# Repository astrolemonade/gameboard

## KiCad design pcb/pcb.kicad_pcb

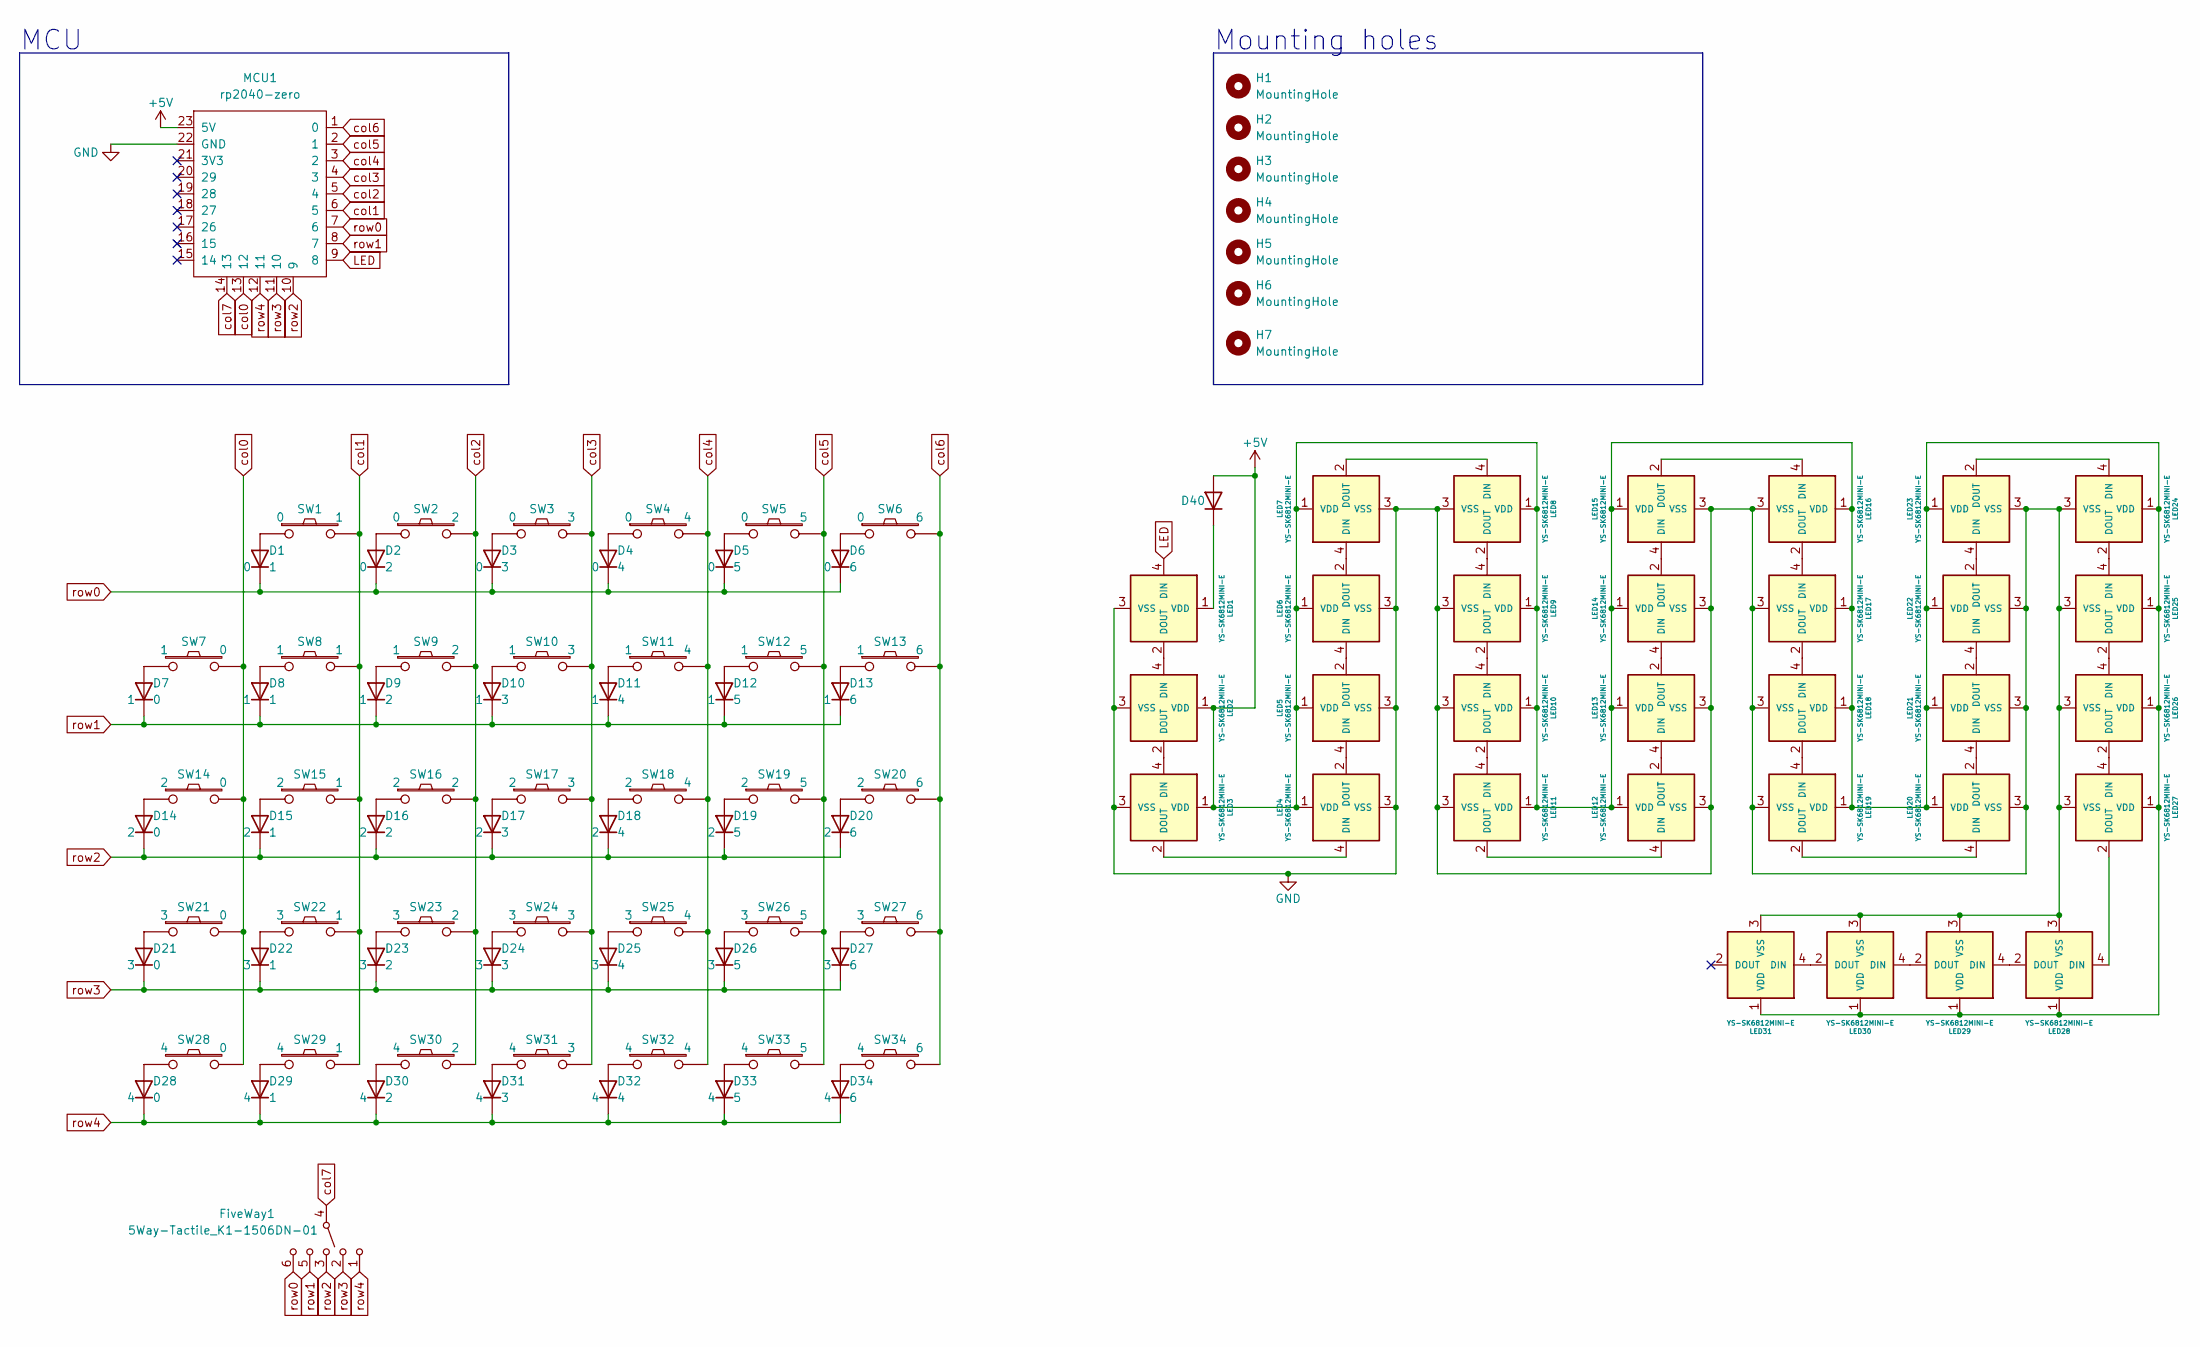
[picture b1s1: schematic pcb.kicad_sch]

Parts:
D1, D2, D3, D4, D5, D6, D7, D8, D9, D10, D11, D12, D13, D14, D15, D16, D17, D18, D19, D20, D21, D22, D23, D24, D25, D26, D27, D28, D29, D30, D31, D32, D33, D34, D40: D; Diode_1N4148-SOD123
FiveWay1: 5Way-Tactile_K1-1506DN-01; Button_5way
H1, H2, H3, H4, H5, H6, H7: MountingHole; Hole_M2-TH
LED1, LED2, LED3, LED4, LED5, LED6, LED7, LED8, LED9, LED10, LED11, LED12, LED13, LED14, LED15, LED16, LED17, LED18, LED19, LED20, LED21, LED22, LED23, LED24, LED25, LED26, LED27, LED28, LED29, LED30, LED31: YS-SK6812MINI-E; LED_SK6812-MINI-E
MCU1: rp2040-zero; MCU_rp2040-zero-tht
SW1, SW2, SW3, SW4, SW5, SW6, SW7, SW8, SW9, SW10, SW11, SW12, SW13, SW14, SW15, SW16, SW17, SW18, SW19, SW20, SW21, SW22, SW23, SW24, SW25, SW26, SW27, SW31, SW32, SW33, SW34: Switch; Switch_MXKS-hotswap-south-ks3d
SW28, SW29, SW30: Switch; Button_Push-6mm

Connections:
+5V: D40.2 (A), LED2.1 (VDD), LED3.1 (VDD), LED4.1 (VDD), LED5.1 (VDD), LED6.1 (VDD), LED7.1 (VDD), LED8.1 (VDD), LED9.1 (VDD), LED10.1 (VDD), LED11.1 (VDD), LED12.1 (VDD), LED13.1 (VDD), LED14.1 (VDD), LED15.1 (VDD), LED16.1 (VDD), LED17.1 (VDD), LED18.1 (VDD), LED19.1 (VDD), LED20.1 (VDD), LED21.1 (VDD), LED22.1 (VDD), LED23.1 (VDD), LED24.1 (VDD), LED25.1 (VDD), LED26.1 (VDD), LED27.1 (VDD), LED28.1 (VDD), LED29.1 (VDD), LED30.1 (VDD), LED31.1 (VDD), MCU1.23 (5V)
GND: LED1.3 (VSS), LED2.3 (VSS), LED3.3 (VSS), LED4.3 (VSS), LED5.3 (VSS), LED6.3 (VSS), LED7.3 (VSS), LED8.3 (VSS), LED9.3 (VSS), LED10.3 (VSS), LED11.3 (VSS), LED12.3 (VSS), LED13.3 (VSS), LED14.3 (VSS), LED15.3 (VSS), LED16.3 (VSS), LED17.3 (VSS), LED18.3 (VSS), LED19.3 (VSS), LED20.3 (VSS), LED21.3 (VSS), LED22.3 (VSS), LED23.3 (VSS), LED24.3 (VSS), LED25.3 (VSS), LED26.3 (VSS), LED27.3 (VSS), LED28.3 (VSS), LED29.3 (VSS), LED30.3 (VSS), LED31.3 (VSS), MCU1.22 (GND)
LED: LED1.4 (DIN), MCU1.9 (8)
unnamed: D1.2 (A), SW1.1
unnamed: D2.2 (A), SW2.1
unnamed: D3.2 (A), SW3.1
unnamed: D4.2 (A), SW4.1
unnamed: D5.2 (A), SW5.1
unnamed: D6.2 (A), SW6.1
unnamed: D7.2 (A), SW7.1
unnamed: D8.2 (A), SW8.1
unnamed: D9.2 (A), SW9.1
unnamed: D10.2 (A), SW10.1
unnamed: D11.2 (A), SW11.1
unnamed: D12.2 (A), SW12.1
unnamed: D13.2 (A), SW13.1
unnamed: D14.2 (A), SW14.1
unnamed: D15.2 (A), SW15.1
unnamed: D16.2 (A), SW16.1
unnamed: D17.2 (A), SW17.1
unnamed: D18.2 (A), SW18.1
unnamed: D19.2 (A), SW19.1
unnamed: D20.2 (A), SW20.1
unnamed: D21.2 (A), SW21.1
unnamed: D22.2 (A), SW22.1
unnamed: D23.2 (A), SW23.1
unnamed: D24.2 (A), SW24.1
unnamed: D25.2 (A), SW25.1
unnamed: D26.2 (A), SW26.1
unnamed: D27.2 (A), SW27.1
unnamed: D28.2 (A), SW28.1
unnamed: D29.2 (A), SW29.1
unnamed: D30.2 (A), SW30.1
unnamed: D31.2 (A), SW31.1
unnamed: D32.2 (A), SW32.1
unnamed: D33.2 (A), SW33.1
unnamed: D34.2 (A), SW34.1
unnamed: D40.1 (K), LED1.1 (VDD)
unnamed: LED1.2 (DOUT), LED2.4 (DIN)
unnamed: LED2.2 (DOUT), LED3.4 (DIN)
unnamed: LED3.2 (DOUT), LED4.4 (DIN)
unnamed: LED4.2 (DOUT), LED5.4 (DIN)
unnamed: LED5.2 (DOUT), LED6.4 (DIN)
unnamed: LED6.2 (DOUT), LED7.4 (DIN)
unnamed: LED7.2 (DOUT), LED8.4 (DIN)
unnamed: LED8.2 (DOUT), LED9.4 (DIN)
unnamed: LED9.2 (DOUT), LED10.4 (DIN)
unnamed: LED10.2 (DOUT), LED11.4 (DIN)
unnamed: LED11.2 (DOUT), LED12.4 (DIN)
unnamed: LED12.2 (DOUT), LED13.4 (DIN)
unnamed: LED13.2 (DOUT), LED14.4 (DIN)
unnamed: LED14.2 (DOUT), LED15.4 (DIN)
unnamed: LED15.2 (DOUT), LED16.4 (DIN)
unnamed: LED16.2 (DOUT), LED17.4 (DIN)
unnamed: LED17.2 (DOUT), LED18.4 (DIN)
unnamed: LED18.2 (DOUT), LED19.4 (DIN)
unnamed: LED19.2 (DOUT), LED20.4 (DIN)
unnamed: LED20.2 (DOUT), LED21.4 (DIN)
unnamed: LED21.2 (DOUT), LED22.4 (DIN)
unnamed: LED22.2 (DOUT), LED23.4 (DIN)
unnamed: LED23.2 (DOUT), LED24.4 (DIN)
unnamed: LED24.2 (DOUT), LED25.4 (DIN)
unnamed: LED25.2 (DOUT), LED26.4 (DIN)
unnamed: LED26.2 (DOUT), LED27.4 (DIN)
unnamed: LED27.2 (DOUT), LED28.4 (DIN)
unnamed: LED28.2 (DOUT), LED29.4 (DIN)
unnamed: LED29.2 (DOUT), LED30.4 (DIN)
unnamed: LED30.2 (DOUT), LED31.4 (DIN)
col0: MCU1.13 (12), SW7.2, SW14.2, SW21.2, SW28.2
col1: MCU1.6 (5), SW1.2, SW8.2, SW15.2, SW22.2, SW29.2
col2: MCU1.5 (4), SW2.2, SW9.2, SW16.2, SW23.2, SW30.2
col3: MCU1.4 (3), SW3.2, SW10.2, SW17.2, SW24.2, SW31.2
col4: MCU1.3 (2), SW4.2, SW11.2, SW18.2, SW25.2, SW32.2
col5: MCU1.2 (1), SW5.2, SW12.2, SW19.2, SW26.2, SW33.2
col6: MCU1.1 (0), SW6.2, SW13.2, SW20.2, SW27.2, SW34.2
col7: FiveWay1.4, MCU1.14 (13)
row0: D1.1 (K), D2.1 (K), D3.1 (K), D4.1 (K), D5.1 (K), D6.1 (K), FiveWay1.6, MCU1.7 (6)
row1: D7.1 (K), D8.1 (K), D9.1 (K), D10.1 (K), D11.1 (K), D12.1 (K), D13.1 (K), FiveWay1.5, MCU1.8 (7)
row2: D14.1 (K), D15.1 (K), D16.1 (K), D17.1 (K), D18.1 (K), D19.1 (K), D20.1 (K), FiveWay1.3, MCU1.10 (9)
row3: D21.1 (K), D22.1 (K), D23.1 (K), D24.1 (K), D25.1 (K), D26.1 (K), D27.1 (K), FiveWay1.2, MCU1.11 (10)
row4: D28.1 (K), D29.1 (K), D30.1 (K), D31.1 (K), D32.1 (K), D33.1 (K), D34.1 (K), FiveWay1.1, MCU1.12 (11)

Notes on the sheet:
Mounting holes
MCU

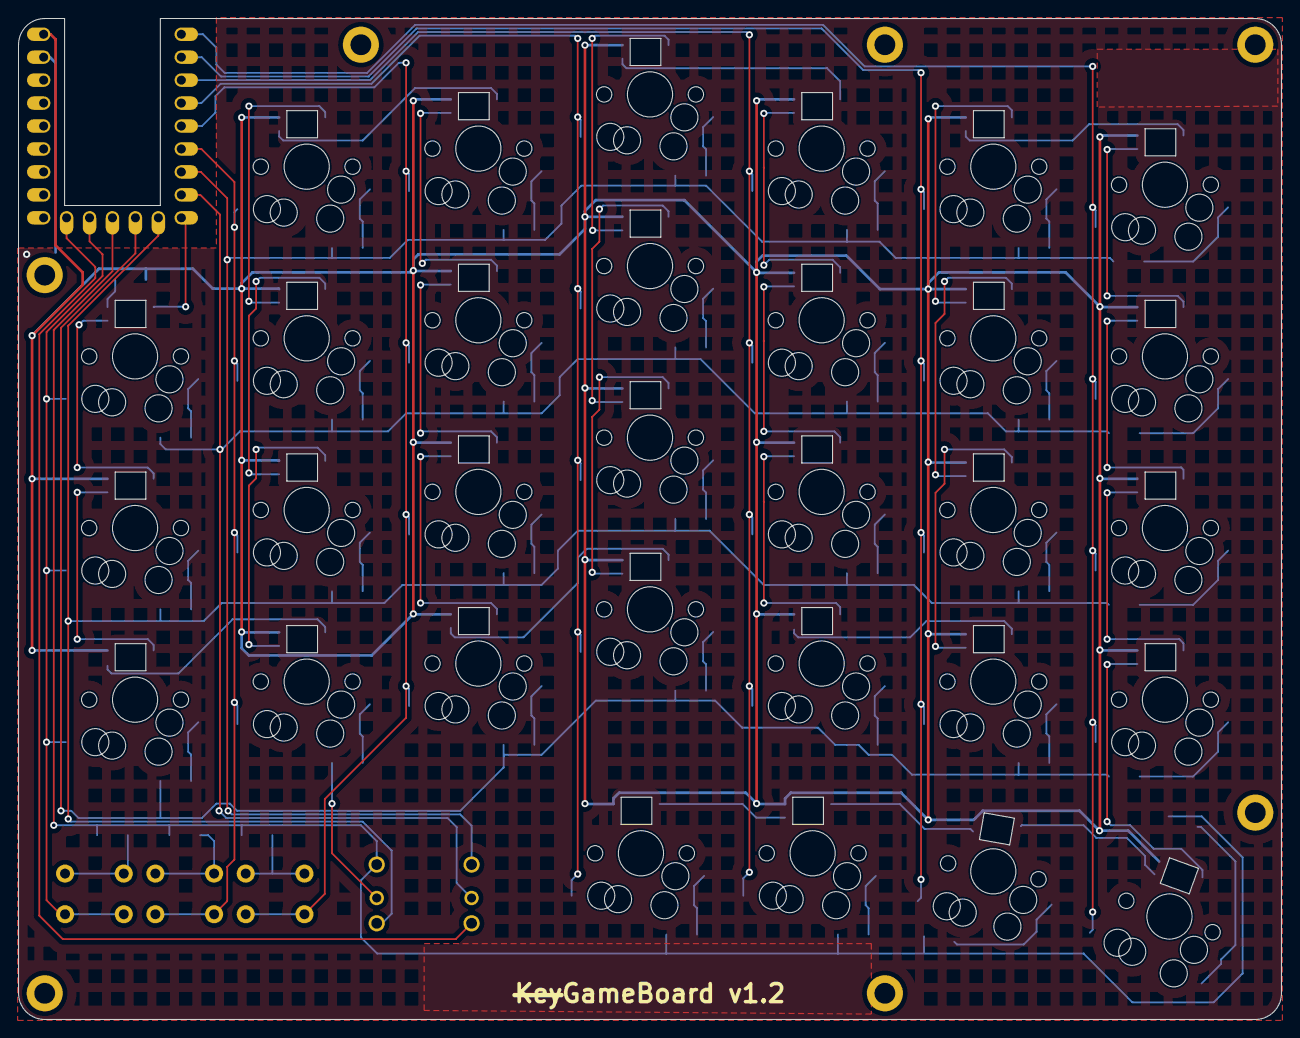
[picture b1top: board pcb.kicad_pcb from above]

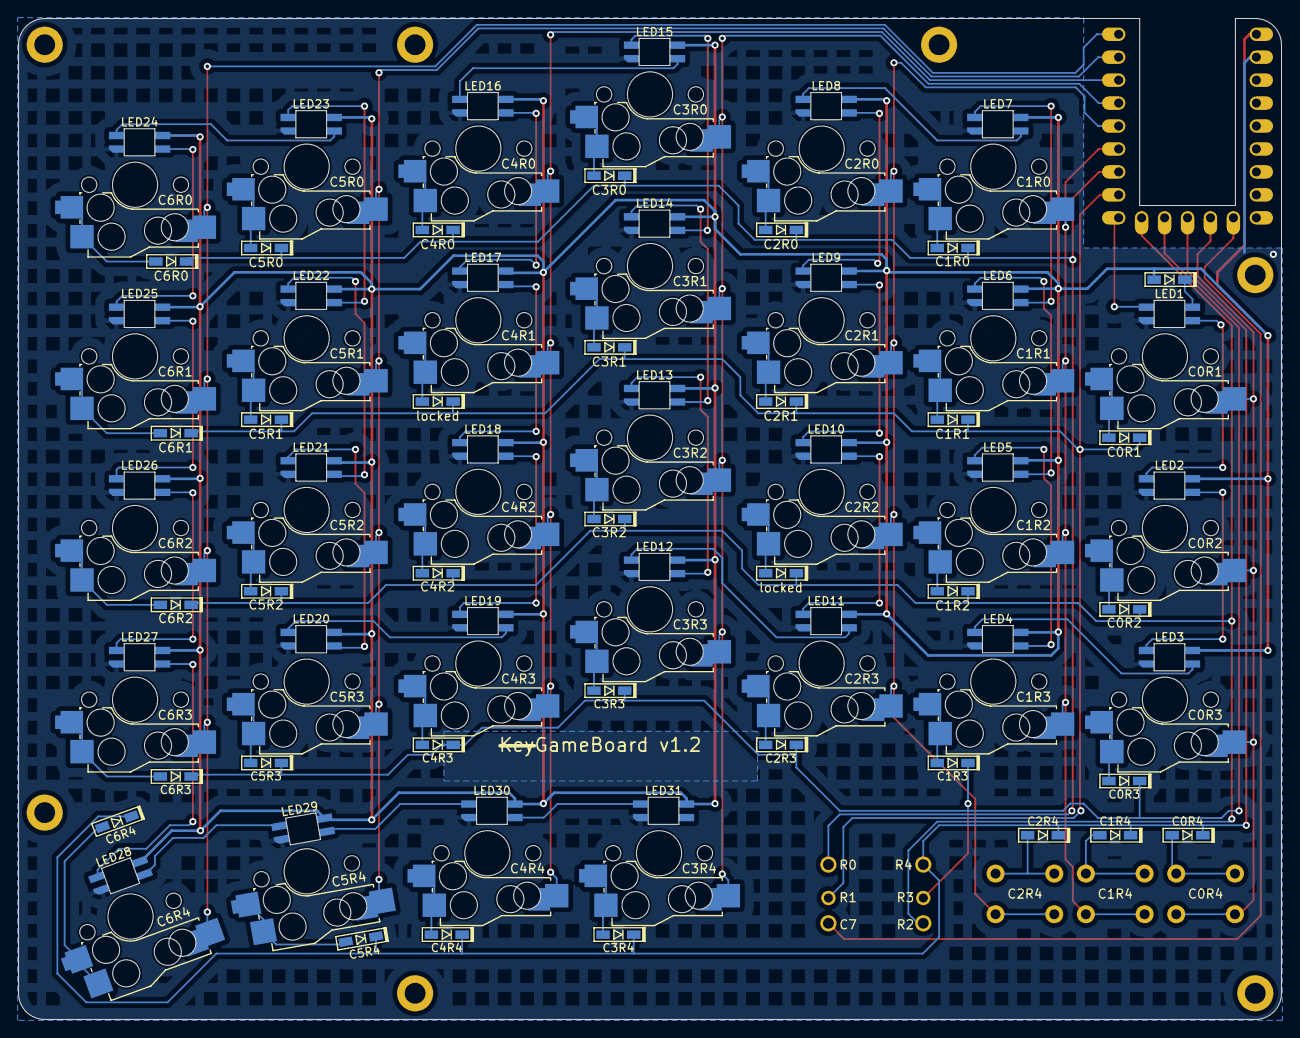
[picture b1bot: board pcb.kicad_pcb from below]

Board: 2 copper layers, 139.8 x 110.8 mm, 109 parts (66 on the bottom side), 81 nets.

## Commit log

2024-01-02 update 3d models
